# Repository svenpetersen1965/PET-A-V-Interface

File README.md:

# PET-A-V-Interface
And A/V Interface for Commodore PET computers
This is a <b>preliminary release</b>. The electronics is fully functional, but the test documentation might require some tweaking. 

The prupose of this project is providing video and audio (CB2) outputs for the Commodore PET computers. The non-CRTC machines generate video outputs, which can be mixed to resemble an NTSC video signal. The resulting signal can be displayed with NTSC monitors or suitable video to HDMI converters.

The internal video signal of the CRTC machines is not following any video standards. Thus it requires to modify the CRTC parameters in the EDIT ROM. The disavantage of these modiied settings is, that the internal monitor does not synchronize with them. It is mandatory to disconnect the video and the supply voltage for the monitor if run with PAL or NTSC parameters for more than just a few minutes.

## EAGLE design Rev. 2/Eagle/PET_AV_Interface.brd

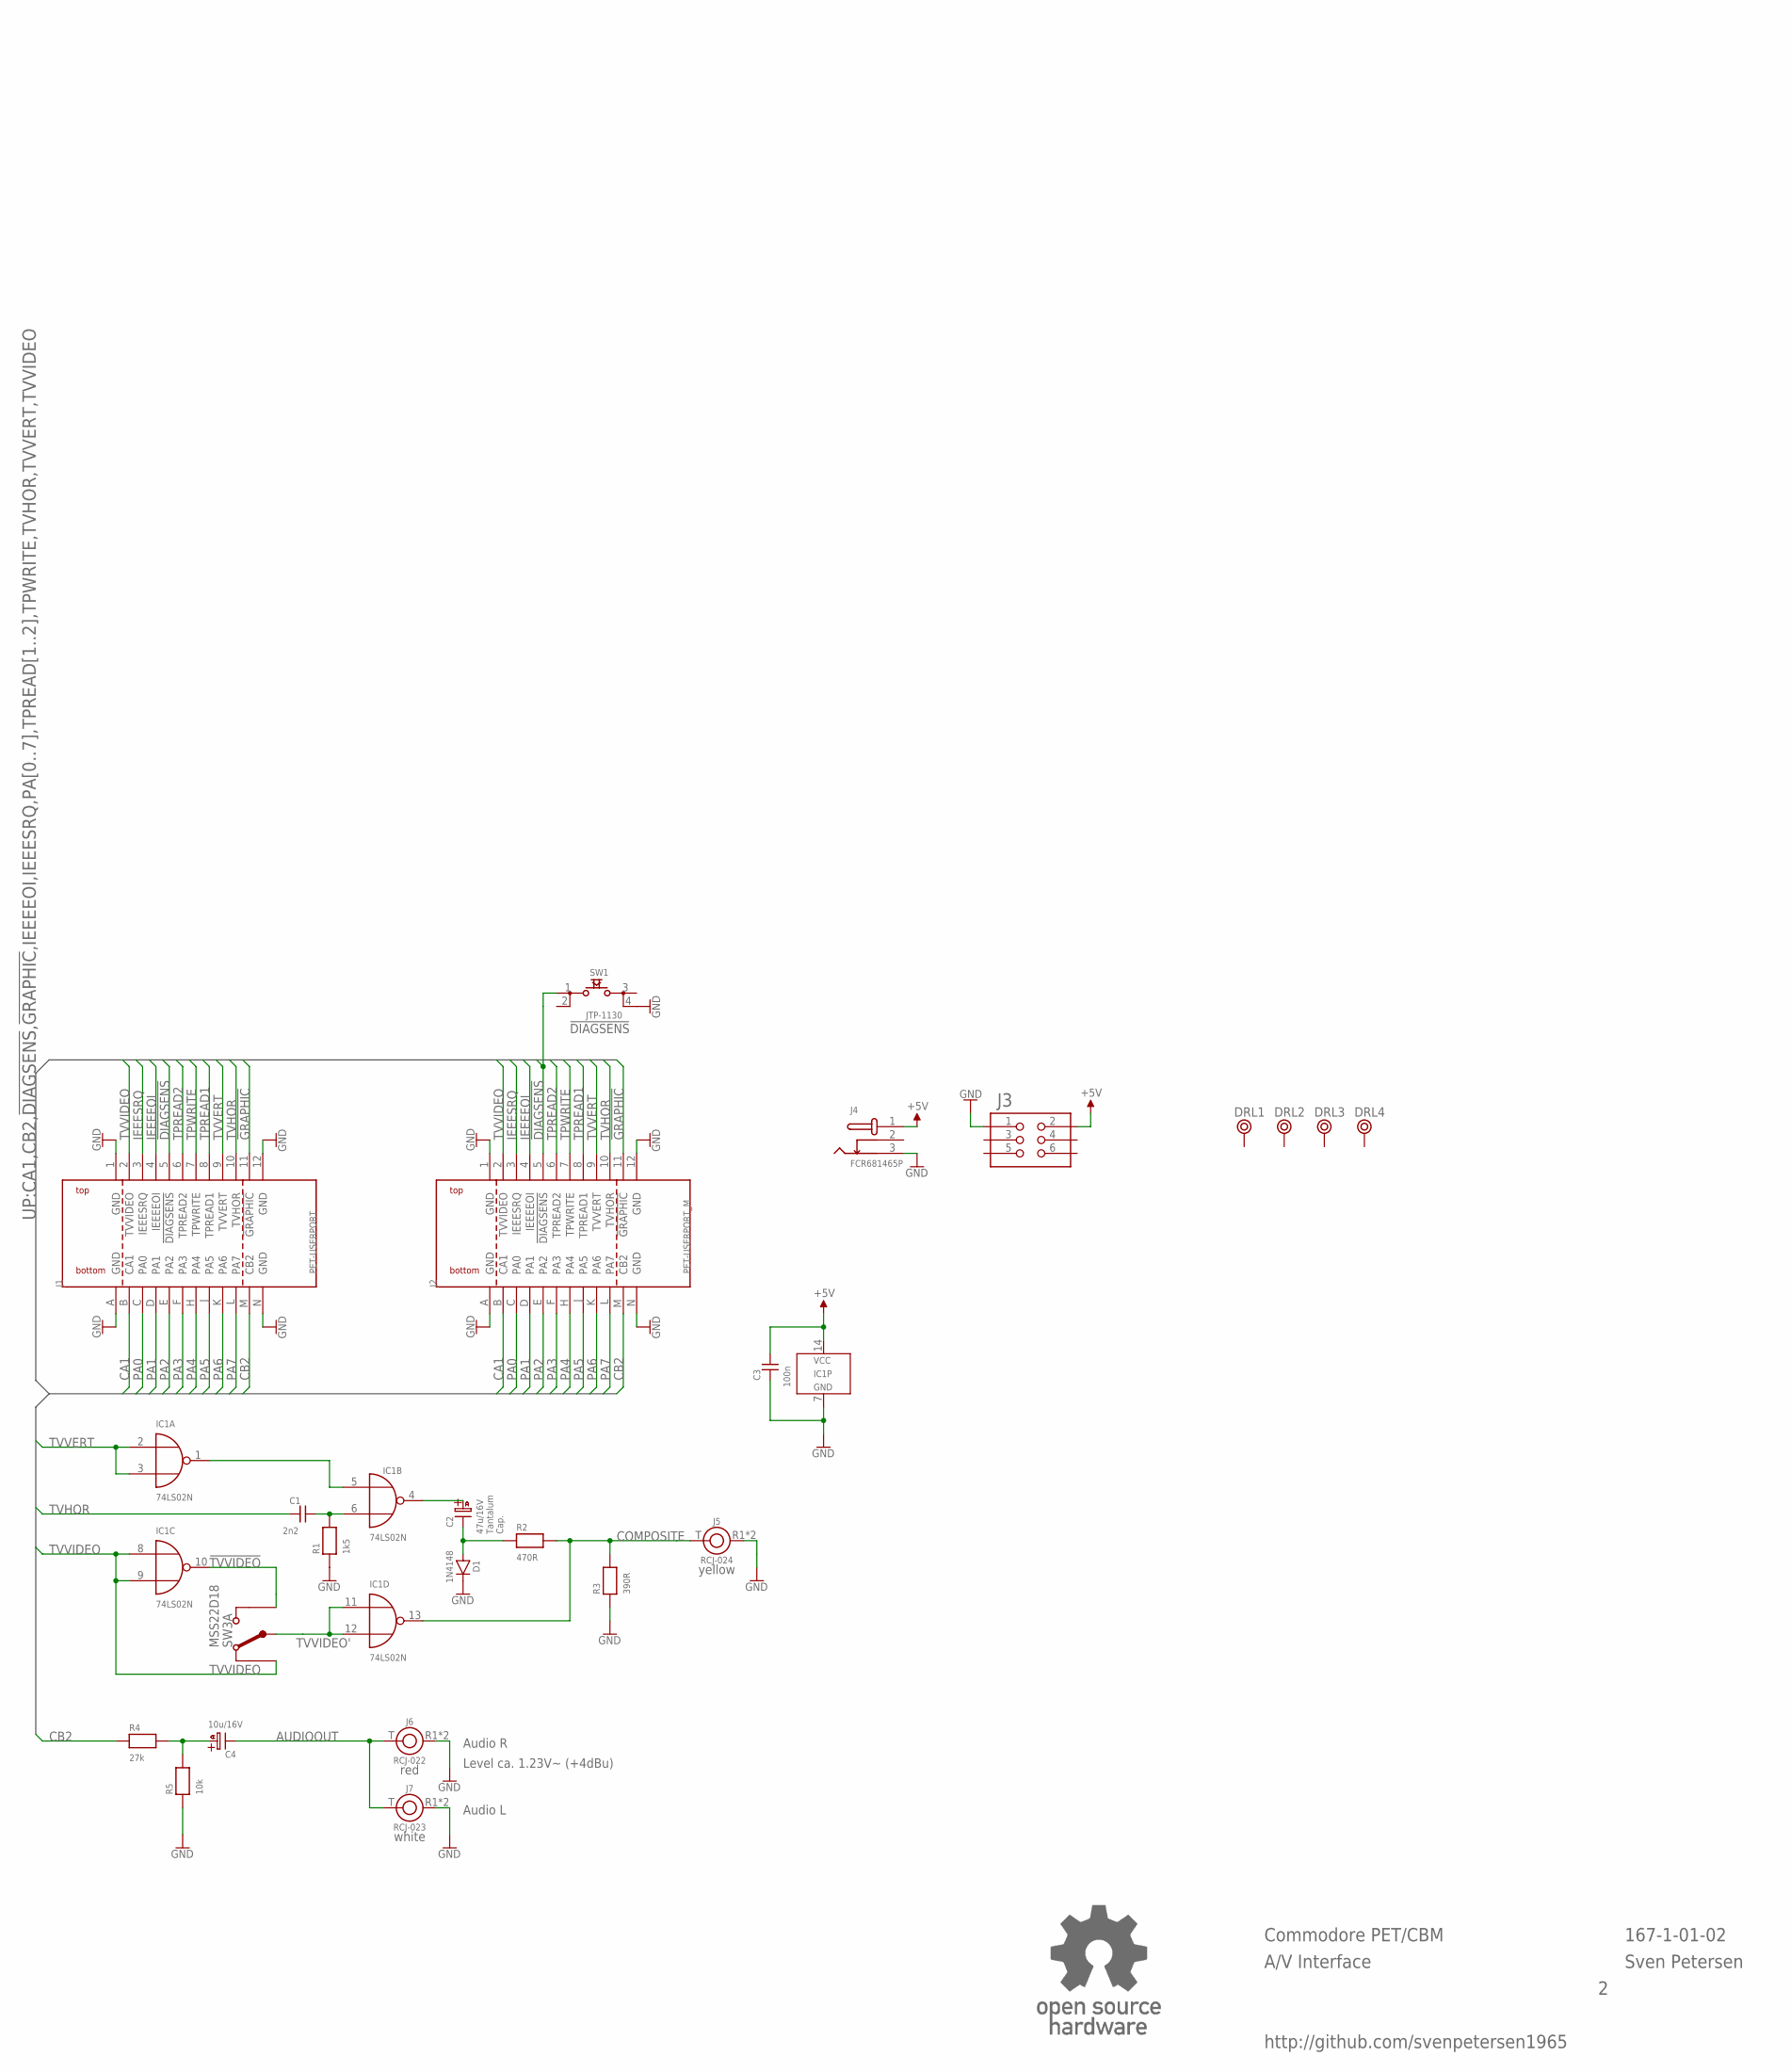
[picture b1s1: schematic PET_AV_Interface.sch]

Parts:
C1: 2n2; C-2,5
C2: 47u/16V; C5,0/2,0
C3: 100n; C-2,5
C4: 10u/16V; C5,0/2,0
D1: 1N4148; DO-35/3
DRL1, DRL2, DRL3, DRL4: BOHR3,5
IC1: 74LS02N; DIL-14
J1: PET-USERPORT; USERPORT
J2: PET-USERPORT_M; USERPORT_M
J3: 2X03WV
J4: FCR681465P
J5: RCJ-024; RCJ-02X
J6: RCJ-022; RCJ-02X
J7: RCJ-023; RCJ-02X
R1: 1k5; R-10
R2: 470R; R-10
R3: 390R; R-10
R4: 27k; R-10
R5: 10k; R-10
SW1: JTP-1130
SW3: MSS22D18; DPDT_9MM
U$2: OPEN_SOURCE_HW; OPENHW

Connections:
!DIAGSENS: J1.5 (!DIAGSENS), J2.5 (!DIAGSENS), SW1.1
!GRAPHIC: J1.11 (!GRAPHIC), J2.11 (!GRAPHIC)
!TVVERT': IC1.1 (O), IC1.5 (I0)
!TVVIDEO: IC1.10 (O), SW3.1 (UP)
+5V: C3.2, IC1.14 (VCC), J3.2, J4.1
AUDIOOUT: C4.K (-), J6.T, J7.T
CA1: J1.B (CA1), J2.B (CA1)
CB2: J1.M (CB2), J2.M (CB2), R4.1
COMPOSITE: IC1.13 (O), J5.T, R2.2, R3.2
GND: C3.1, D1.K, IC1.7 (GND), J1.1 (GND), J1.12 (GND), J1.A (GND), J1.N (GND), J2.1 (GND), J2.12 (GND), J2.A (GND), J2.N (GND), J3.1, J4.3, J5.R1 (R), J5.R2 (R), J6.R1 (R), J6.R2 (R), J7.R1 (R), J7.R2 (R), R1.1, R3.1, R5.1, SW1.4
IEEEEOI: J1.4 (IEEEEOI), J2.4 (IEEEEOI)
IEEESRQ: J1.3 (IEEESRQ), J2.3 (IEEESRQ)
unnamed: C4.A (+), R4.2, R5.2
unnamed: C1.2, IC1.6 (I1), R1.2
unnamed: C2.A (+), IC1.4 (O)
unnamed: C2.K (-), D1.A, R2.1
PA0: J1.C (PA0), J2.C (PA0)
PA1: J1.D (PA1), J2.D (PA1)
PA2: J1.E (PA2), J2.E (PA2)
PA3: J1.F (PA3), J2.F (PA3)
PA4: J1.H (PA4), J2.H (PA4)
PA5: J1.J (PA5), J2.J (PA5)
PA6: J1.K (PA6), J2.K (PA6)
PA7: J1.L (PA7), J2.L (PA7)
TPREAD1: J1.8 (TPREAD1), J2.8 (TPREAD1)
TPREAD2: J1.6 (TPREAD2), J2.6 (TPREAD2)
TPWRITE: J1.7 (TPWRITE), J2.7 (TPWRITE)
TVHOR: C1.1, J1.10 (TVHOR), J2.10 (TVHOR)
TVVERT: IC1.2 (I0), IC1.3 (I1), J1.9 (TVVERT), J2.9 (TVVERT)
TVVIDEO: IC1.8 (I0), IC1.9 (I1), J1.2 (TVVIDEO), J2.2 (TVVIDEO), SW3.3 (DWN)
TVVIDEO': IC1.11 (I0), IC1.12 (I1), SW3.2 (COM)

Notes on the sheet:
http://github.com/svenpetersen1965
Commodore PET/CBM
A/V Interface
Sven Petersen
167-1-01-02
yellow
red
white
Audio R
Audio L
Level ca. 1.23V~ (+4dBu)
Tantalum Cap.

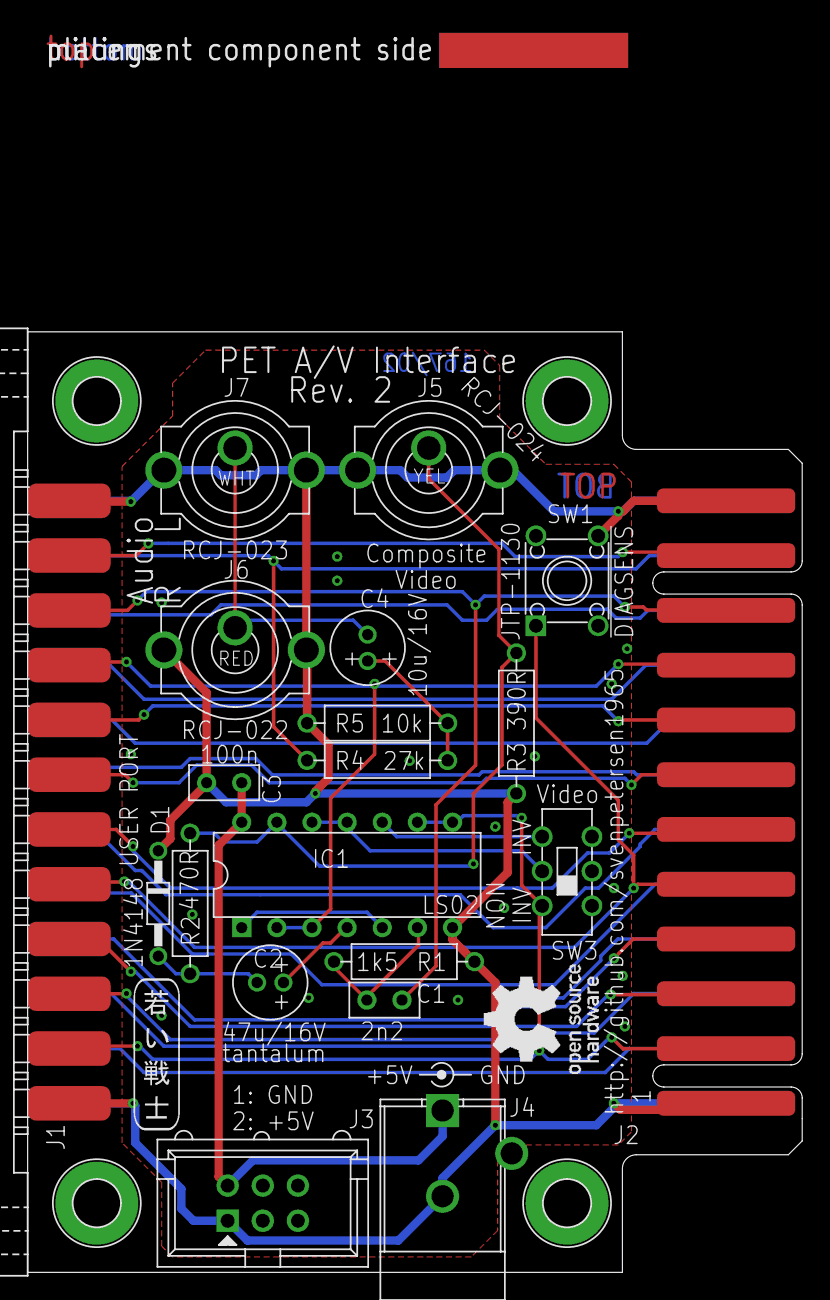
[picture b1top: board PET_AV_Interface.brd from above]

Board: 2 copper layers, 56.0 x 68.0 mm, 28 parts (0 on the bottom side), 31 nets.

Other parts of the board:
U$22: PCB-TITLE/
U$23: 2LAYER
U$26: SVEN_TAG

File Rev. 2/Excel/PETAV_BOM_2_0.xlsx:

PET A/V Interface Rev. 2
Bill of Material Rev. 2.0
Pos. | Qty | Value | Footprint | Ref.-No. | Comment
1 | 1 | 167-2-01-02 | 2 Layer | PCB Rev. 2 | 2 layer, Cu 35µ, HASL, 43.0mm x 68.0mm, 1.6mm FR4
2 | 1 | 2x3 box header, 2.54mm | 2X03WV | J3 | e.g. Reichelt WSL 6G. Option: Power from tape
3 | 1 | 100n/50V | C-2,5 | C3 | ceramic capacitor, pitch: 2.5mm
4 | 1 | 10k | R-10 | R5 | 1/4W, 1% or better
5 | 1 | 10u/16V | C5,0/2,0 | C4 | aluminum electrolytic, Æ5.0mm/pitch 2.0mm 105°C, l=11mm, e.G. Reichelt RD1C106M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
6 | 1 | 1N4148 | DO-35 | D1 | standard silicon diode
7 | 1 | 1k5 | R-10 | R1 | 1/4W, 1% or better
8 | 1 | 27k | R-10 | R4 | 1/4W, 1% or better
9 | 1 | 2n2 | C-2,5 | C1 | ceramic capacitor, pitch: 2.5mm
10 | 1 | 390R | R-10 | R3 | 1/4W, 1% or better
11 | 1 | 470R | R-10 | R2 | 1/4W, 1% or better
12 | 1 | 47u/16V (Tantalum!) | C5,0/2,0 | C2 | tantalum cap!!! E.g. Reichelt TANTAL 47/16
13 | 1 | 74LS02N | DIL-14 | IC1 | TI or other
14 | 1 | FCR681465P | FCR681465P | J4 | Cliff. 2,5mm/5.5mm barrel connector. E.g. Reichelt CLIFF FCR681465P Option: ext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
15 | 1 | JTP-1130 | JTP-1130 | SW1 | standard TACT switch 6mm x 6mm, height = 13mm, e.g. Reichelt JTP-1130
16 | 1 | MSS22D18 | DPDT_9MM | SW3 | mini slide switch, AliExpress or Amazon. , search term "MSS22D18"
17 | 1 | Edge connector, 2x12, 3.96mm | USERPORT | J1 | edge connector, C64 user port, Ali Express, "series 805" or other
18 | 1 | RCJ-022 | RCJ-02X | J6 | CUI Inc., RCA jack, vertical, red. Mouser: 490-RCJ-022, Digikey: CP-1407-ND. Al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
19 | 1 | RCJ-023 | RCJ-02X | J7 | CUI Inc., RCA jack, vertical, white. Mouser: 490-RCJ-023, Digikey: CP-1408-ND. 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
20 | 1 | RCJ-024 | RCJ-02X | J5 | CUI Inc., RCA jack, vertical, yellow. Mouser: 490-RCJ-024, Digikey: CP-1409-ND.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

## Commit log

2024-07-19 Release of Rev. 2
2024-07-29 Fusion360 files uploaded
